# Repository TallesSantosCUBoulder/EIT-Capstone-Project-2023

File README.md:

# EIT-Capstone-Project-2023

This repository was created for the Electrical Impedance Tomography (EIT) Senior Design Project. The goals of this project were to make open-source hardware and software to reduce the cost of EIT in medical imaging.

## Demo

## Introduction
The EIT project was sponsored by Dr. Talles Santos for Colorado Mesa - Colorado Boulder Partnership engineering senior design class. 

First Year Team: Diego Sena, Keegan Erickson, Jonathan Keleppinger

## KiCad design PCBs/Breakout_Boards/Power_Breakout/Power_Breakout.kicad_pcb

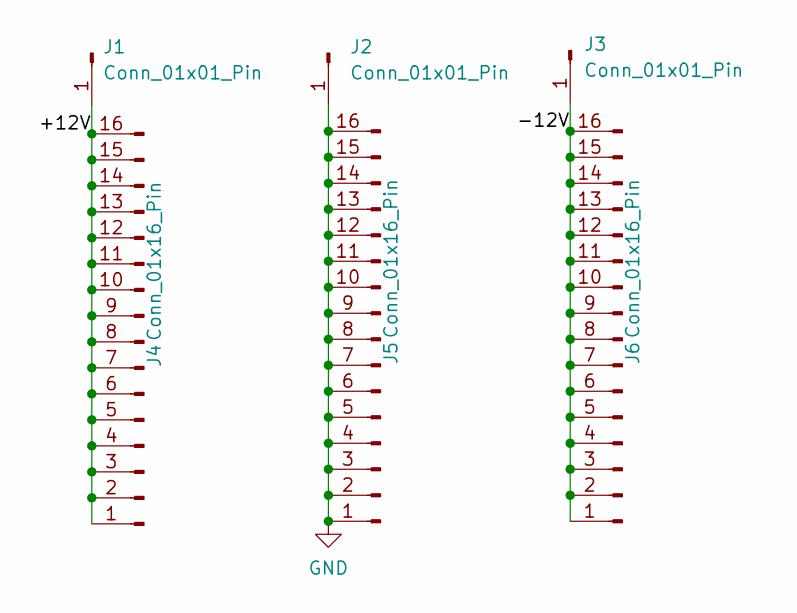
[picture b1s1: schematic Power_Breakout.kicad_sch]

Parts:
J1, J2, J3: Conn_01x01_Pin; PinHeader_1x01_P2.54mm_Vertical
J4, J5, J6: Conn_01x16_Pin; PinHeader_1x16_P2.54mm_Vertical

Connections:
/+12V: J1.1, J4.1, J4.2, J4.3, J4.4, J4.5, J4.6, J4.7, J4.8, J4.9, J4.10, J4.11, J4.12, J4.13, J4.14, J4.15, J4.16
/-12V: J3.1, J6.1, J6.2, J6.3, J6.4, J6.5, J6.6, J6.7, J6.8, J6.9, J6.10, J6.11, J6.12, J6.13, J6.14, J6.15, J6.16
GND: J2.1, J5.1, J5.2, J5.3, J5.4, J5.5, J5.6, J5.7, J5.8, J5.9, J5.10, J5.11, J5.12, J5.13, J5.14, J5.15, J5.16

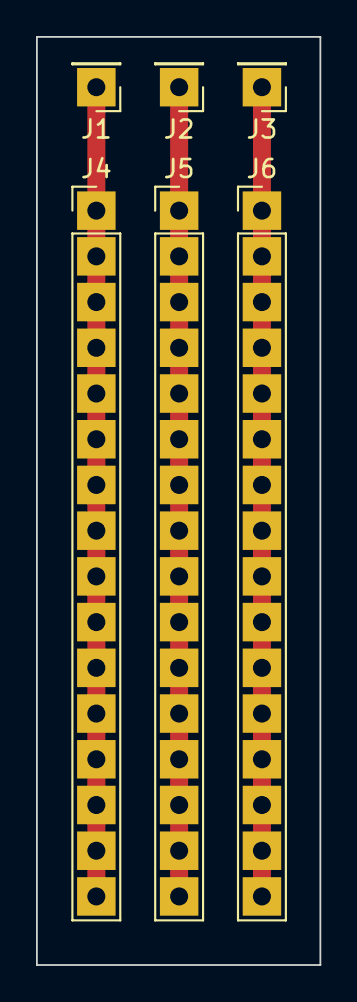
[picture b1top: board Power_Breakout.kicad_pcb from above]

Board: 2 copper layers, 15.7 x 51.6 mm, 6 parts (0 on the bottom side), 3 nets.

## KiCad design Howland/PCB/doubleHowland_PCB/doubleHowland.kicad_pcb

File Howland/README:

The Howland Current source is a Voltage Controlled Current Source

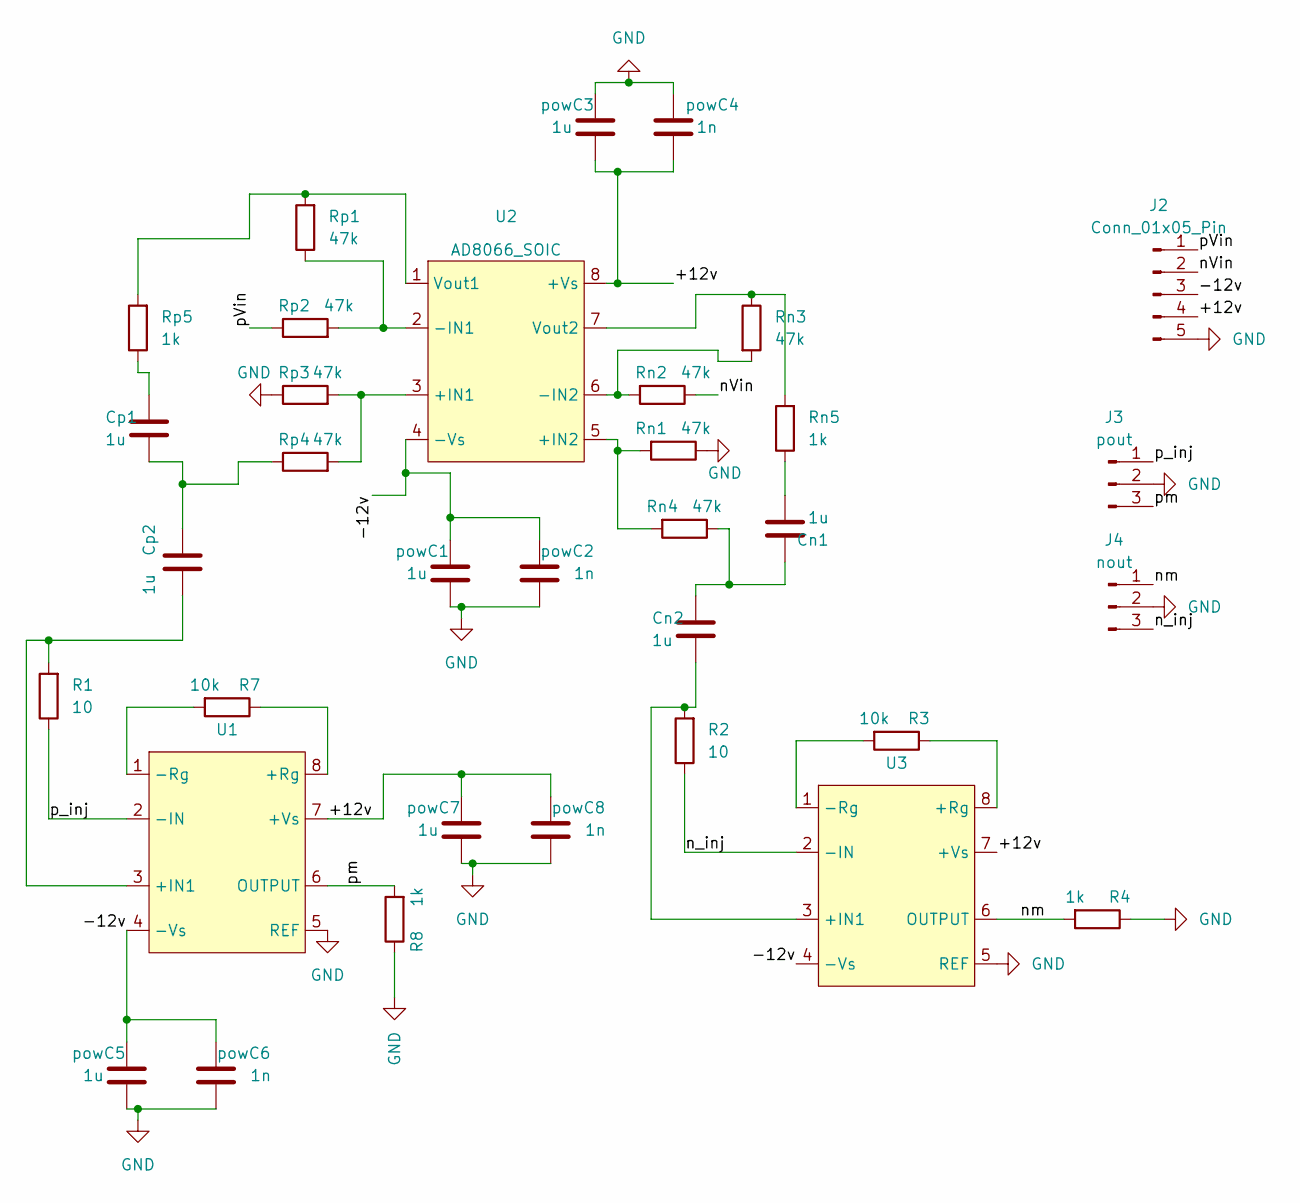
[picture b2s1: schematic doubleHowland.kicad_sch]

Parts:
Cn1, Cn2: 1u; R_Axial_DIN0207_L6.3mm_D2.5mm_P7.62mm_Horizontal
Cp1, Cp2: 1u; R_Axial_DIN0207_L6.3mm_D2.5mm_P7.62mm_Horizontal
J2: Conn_01x05_Pin; PinHeader_1x05_P2.54mm_Vertical
J3: pout; PinHeader_1x03_P2.54mm_Vertical
J4: nout; PinHeader_1x03_P2.54mm_Vertical
R1, R2: 10; R_Axial_DIN0207_L6.3mm_D2.5mm_P10.16mm_Horizontal
R3, R7: 10k; R_Axial_DIN0207_L6.3mm_D2.5mm_P10.16mm_Horizontal
R4, R8: 1k; R_Axial_DIN0207_L6.3mm_D2.5mm_P10.16mm_Horizontal
Rn1, Rn2, Rn3, Rn4: 47k; R_Axial_DIN0207_L6.3mm_D2.5mm_P10.16mm_Horizontal
Rn5: 1k; R_Axial_DIN0207_L6.3mm_D2.5mm_P10.16mm_Horizontal
Rp1, Rp2, Rp3, Rp4: 47k; R_Axial_DIN0207_L6.3mm_D2.5mm_P10.16mm_Horizontal
Rp5: 1k; R_Axial_DIN0207_L6.3mm_D2.5mm_P10.16mm_Horizontal
U1, U3: DIP-8_W7.62mm
U2: AD8066_SOIC; DIP-8_W7.62mm
powC1, powC3, powC5, powC7: 1u; R_Axial_DIN0207_L6.3mm_D2.5mm_P7.62mm_Horizontal
powC2, powC4, powC6, powC8: 1n; R_Axial_DIN0207_L6.3mm_D2.5mm_P7.62mm_Horizontal

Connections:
/+12v: J2.4, U1.7 (+Vs), U2.8 (+Vs), U3.7 (+Vs), powC3.2, powC4.2, powC7.1, powC8.1
/-12v: J2.3, U1.4 (-Vs), U2.4 (-Vs), U3.4 (-Vs), powC1.1, powC2.1, powC5.1, powC6.1
/nVin: J2.2, Rn2.1
/n_inj: J4.3, R2.1, U3.2 (-IN)
/nm: J4.1, R4.2, U3.6 (OUTPUT)
/pVin: J2.1, Rp2.1
/p_inj: J3.1, R1.1, U1.2 (-IN)
/pm: J3.3, R8.2, U1.6 (OUTPUT)
GND: J2.5, J3.2, J4.2, R4.1, R8.1, Rn1.1, Rp3.1, U1.5 (REF), U3.5 (REF), powC1.2, powC2.2, powC3.1, powC4.1, powC5.2, powC6.2, powC7.2, powC8.2
unnamed: Cn1.1, Cn2.1, Rn4.1
unnamed: Cn1.2, Rn5.1
unnamed: Cp1.1, Rp5.1
unnamed: Cp1.2, Cp2.1, Rp4.1
unnamed: Cp2.2, R1.2, U1.3 (+IN1)
unnamed: R7.1, U1.8 (+Rg)
unnamed: R7.2, U1.1 (-Rg)
unnamed: Rp3.2, Rp4.2, U2.3 (+IN1)
unnamed: Rn1.2, Rn4.2, U2.5 (+IN2)
unnamed: Rp1.1, Rp2.2, U2.2 (-IN1)
unnamed: Rn2.2, Rn3.2, U2.6 (-IN2)
unnamed: Rp1.2, Rp5.2, U2.1 (Vout1)
unnamed: Rn3.1, Rn5.2, U2.7 (Vout2)
unnamed: Cn2.2, R2.2, U3.3 (+IN1)
unnamed: R3.1, U3.8 (+Rg)
unnamed: R3.2, U3.1 (-Rg)

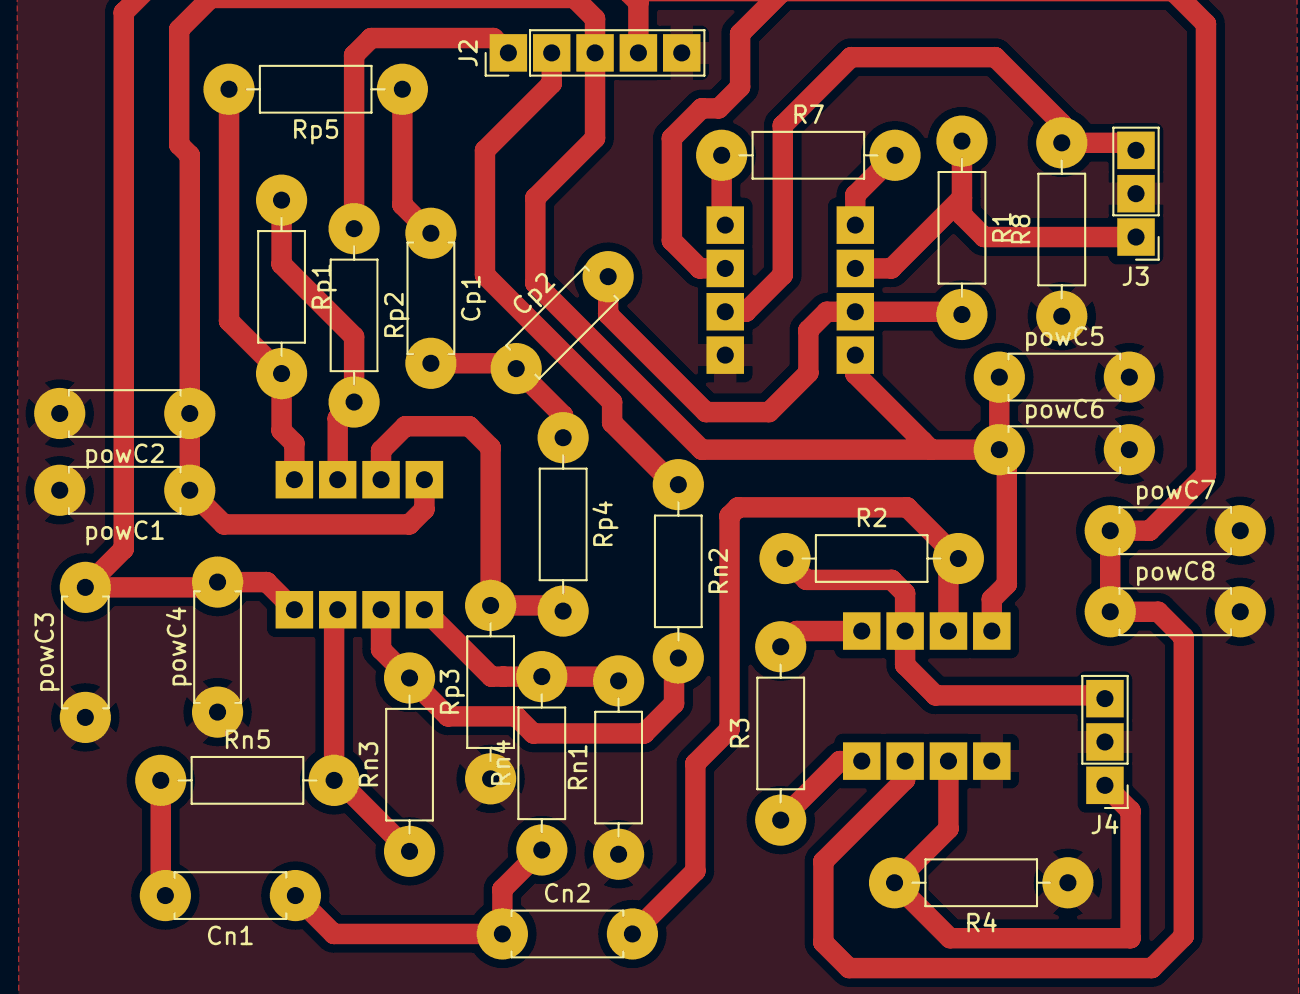
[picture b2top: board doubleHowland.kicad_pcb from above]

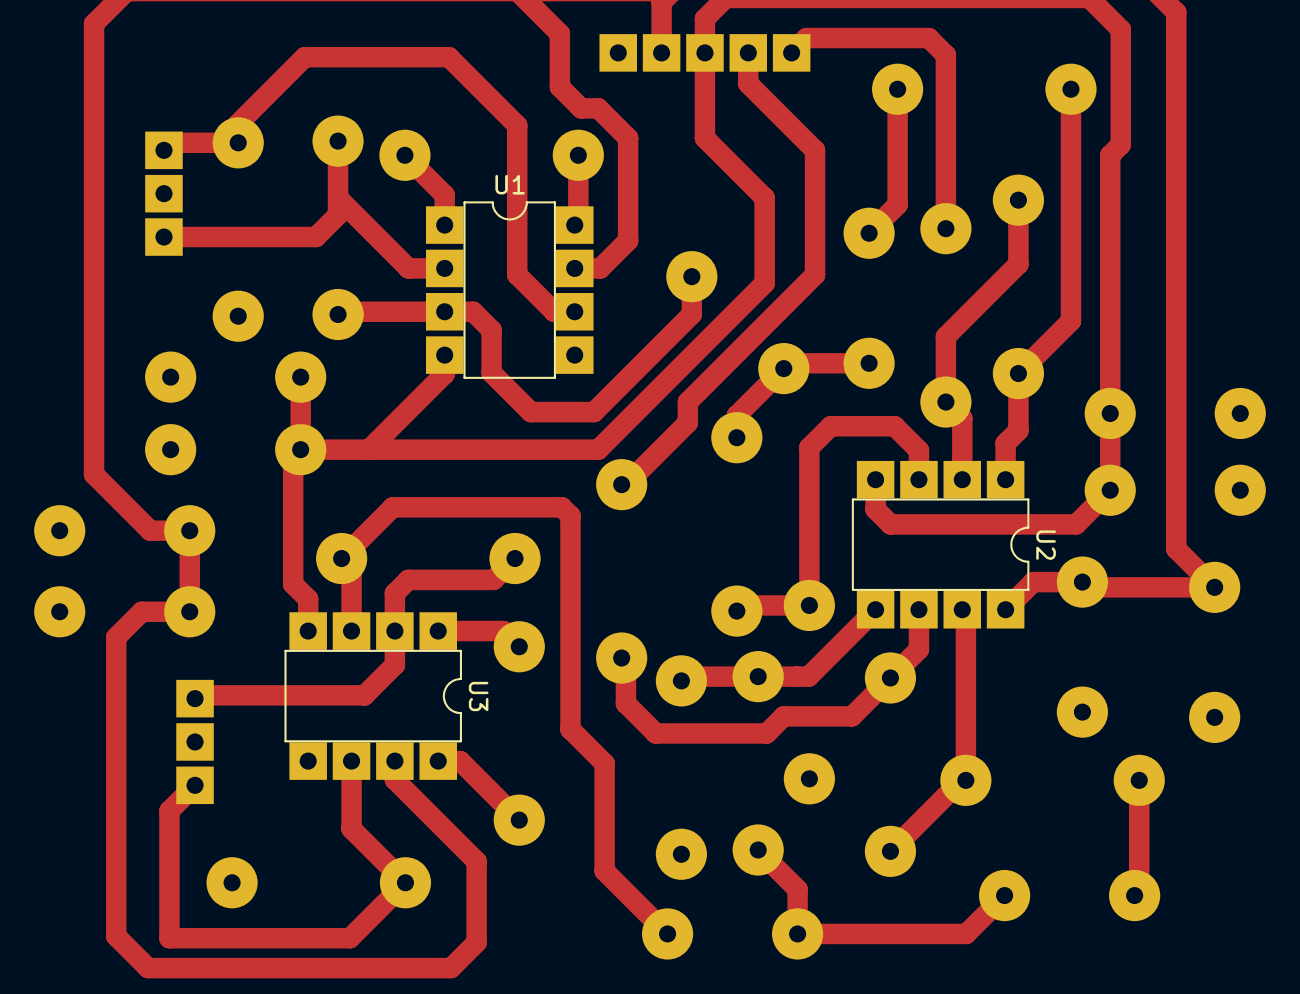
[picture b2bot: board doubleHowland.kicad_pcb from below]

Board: 2 copper layers, 34 parts (3 on the bottom side), 25 nets.

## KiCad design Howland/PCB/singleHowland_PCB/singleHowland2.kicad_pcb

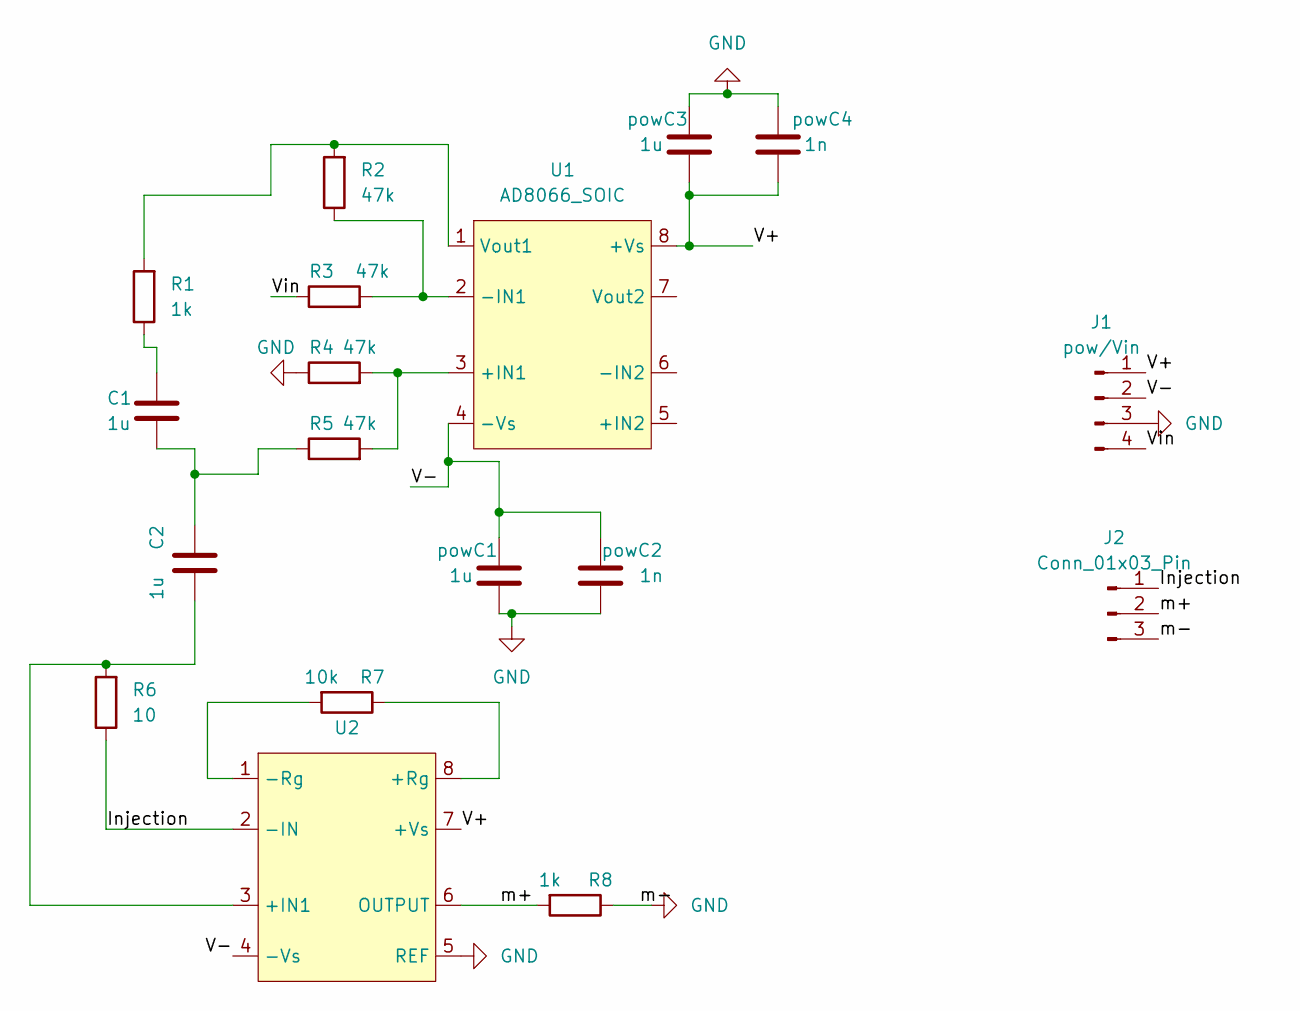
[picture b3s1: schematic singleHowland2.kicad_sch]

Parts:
C1, C2: 1u; R_Axial_DIN0207_L6.3mm_D2.5mm_P7.62mm_Horizontal
J1: pow/Vin; PinHeader_1x04_P2.54mm_Vertical
J2: Conn_01x03_Pin; PinHeader_1x03_P2.54mm_Vertical
R1, R8: 1k; R_Axial_DIN0207_L6.3mm_D2.5mm_P10.16mm_Horizontal
R2, R3, R4, R5: 47k; R_Axial_DIN0207_L6.3mm_D2.5mm_P10.16mm_Horizontal
R6: 10; R_Axial_DIN0207_L6.3mm_D2.5mm_P10.16mm_Horizontal
R7: 10k; R_Axial_DIN0207_L6.3mm_D2.5mm_P10.16mm_Horizontal
U1: AD8066_SOIC; DIP-8_W7.62mm
U2: DIP-8_W7.62mm
powC1, powC3: 1u; R_Axial_DIN0207_L6.3mm_D2.5mm_P7.62mm_Horizontal
powC2, powC4: 1n; R_Axial_DIN0207_L6.3mm_D2.5mm_P7.62mm_Horizontal

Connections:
/Injection: J2.1, R6.1, U2.2 (-IN)
/V+: J1.1, U1.8 (+Vs), U2.7 (+Vs), powC3.2, powC4.2
/V-: J1.2, U1.4 (-Vs), U2.4 (-Vs), powC1.1, powC2.1
/Vin: J1.4, R3.1
/m+: J2.2, R8.2, U2.6 (OUTPUT)
GND: J1.3, J2.3, R4.1, R8.1, U2.5 (REF), powC1.2, powC2.2, powC3.1, powC4.1
unnamed: C1.1, R1.1
unnamed: C1.2, C2.1, R5.1
unnamed: R4.2, R5.2, U1.3 (+IN1)
unnamed: R2.1, R3.2, U1.2 (-IN1)
unnamed: R1.2, R2.2, U1.1 (Vout1)
unnamed: C2.2, R6.2, U2.3 (+IN1)
unnamed: R7.1, U2.8 (+Rg)
unnamed: R7.2, U2.1 (-Rg)

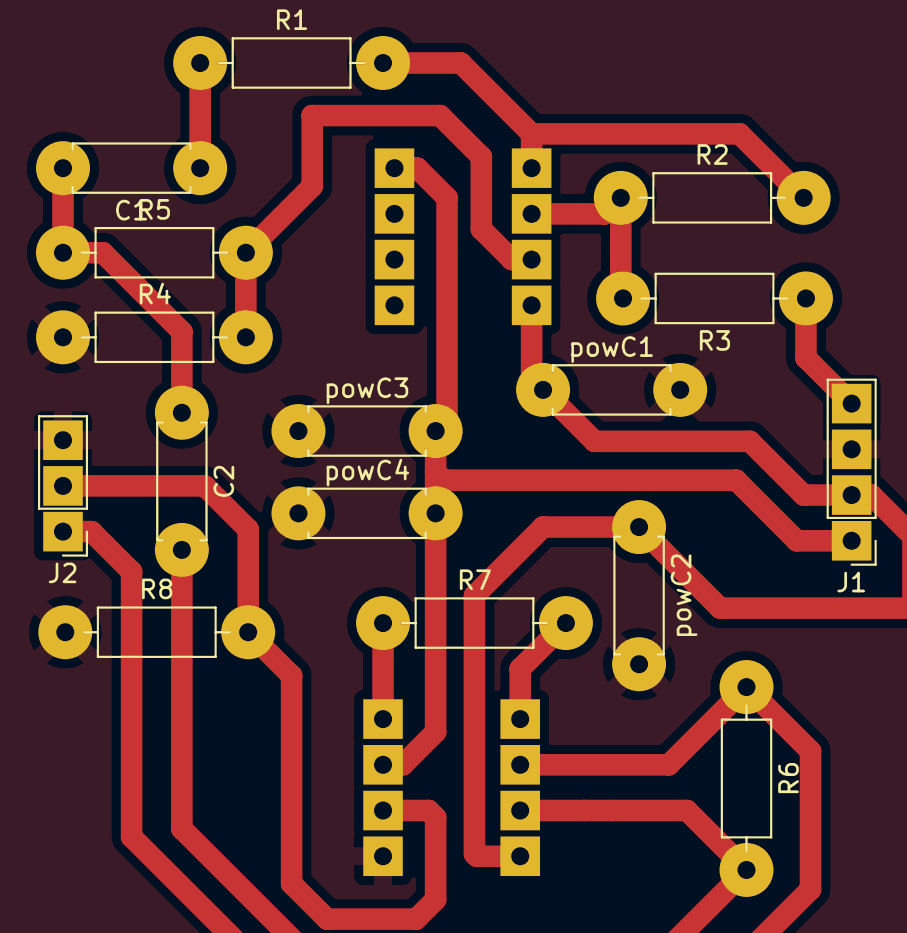
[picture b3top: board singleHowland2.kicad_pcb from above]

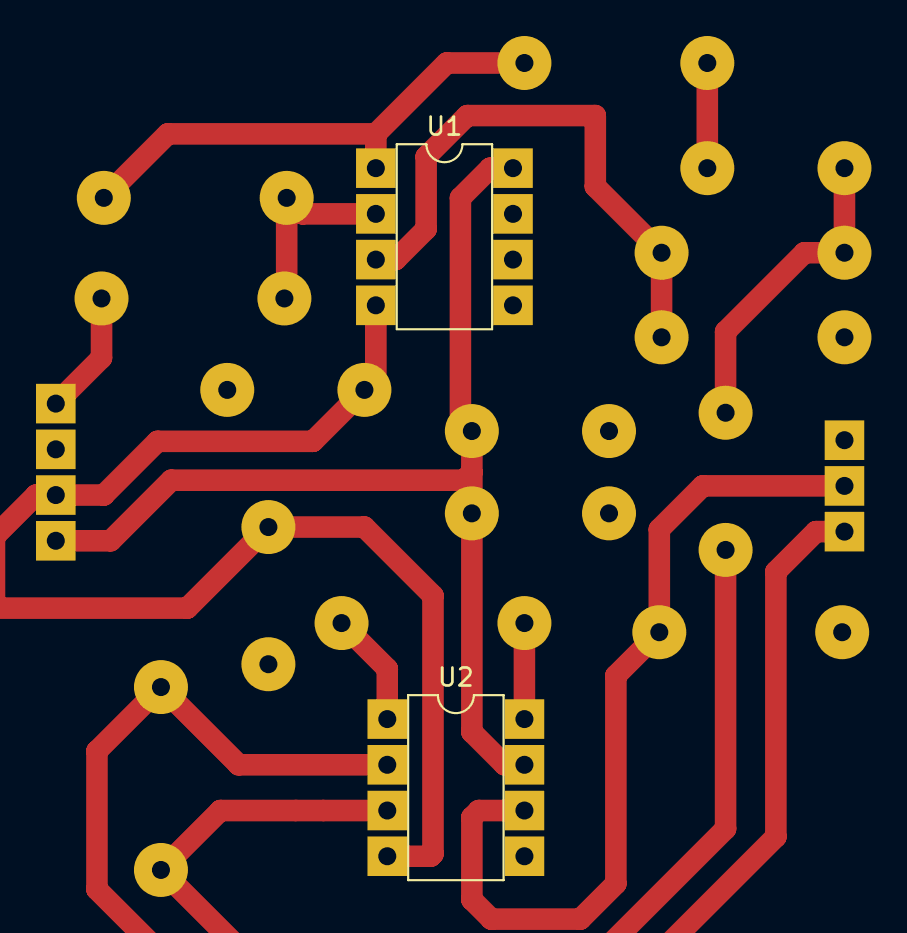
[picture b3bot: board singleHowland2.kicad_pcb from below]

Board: 2 copper layers, 18 parts (2 on the bottom side), 14 nets.

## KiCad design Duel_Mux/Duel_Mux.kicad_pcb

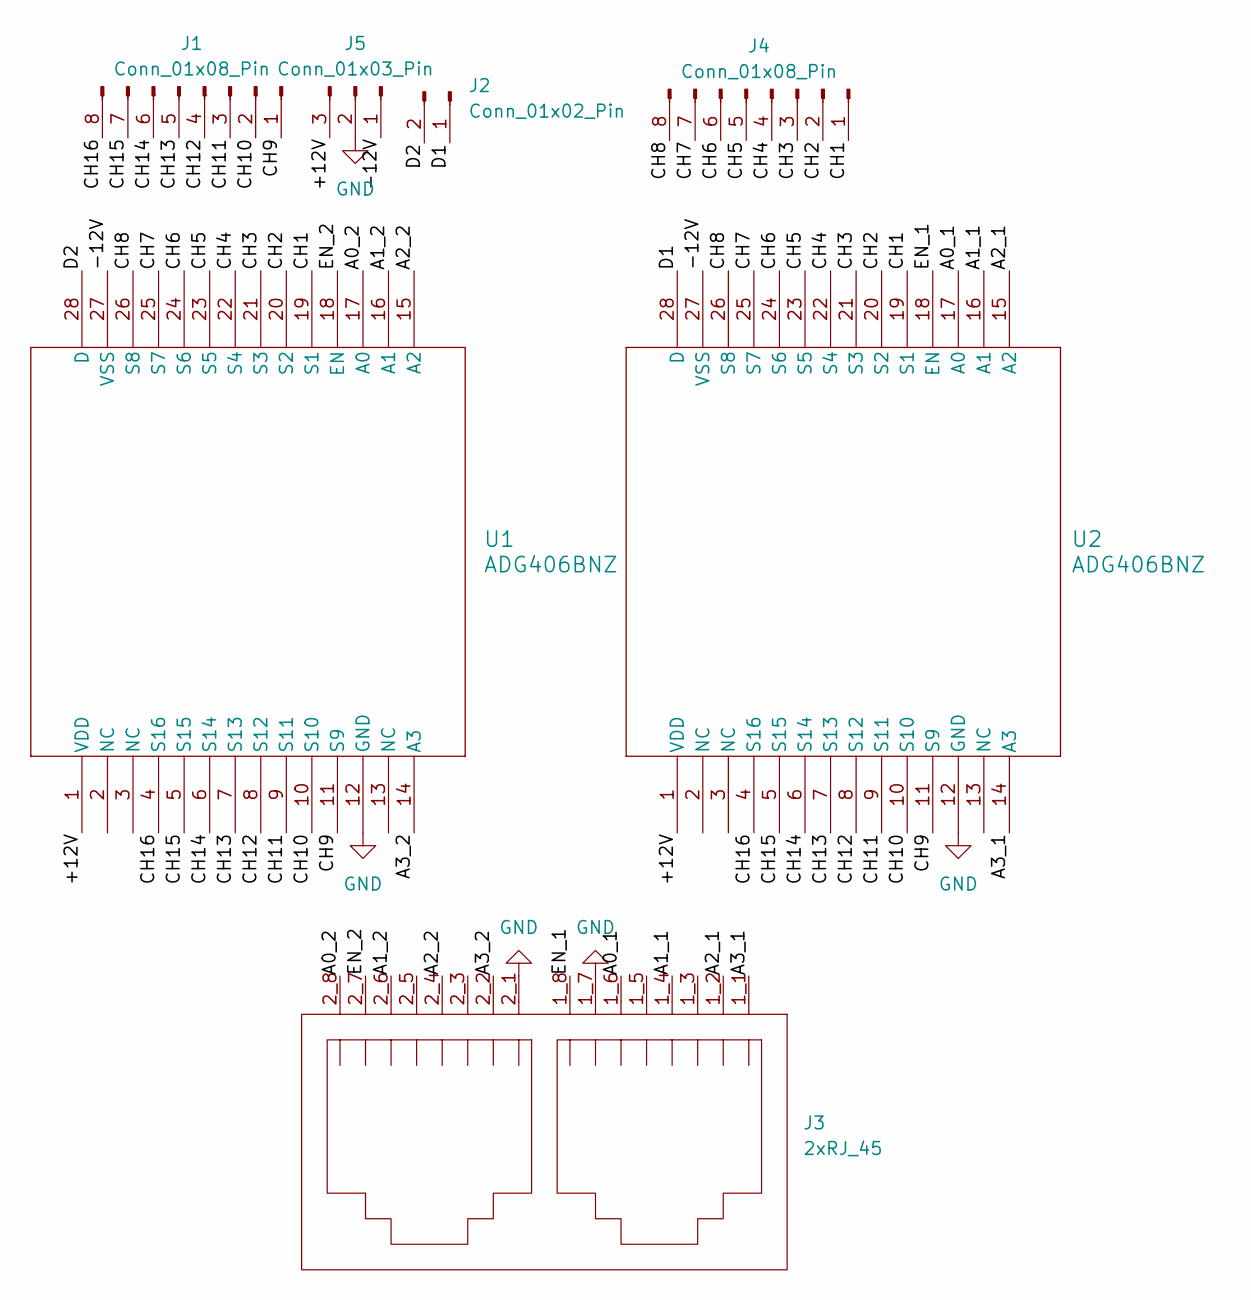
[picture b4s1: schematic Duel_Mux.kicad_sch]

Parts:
J1, J4: Conn_01x08_Pin; PinHeader_1x08_P2.54mm_Vertical
J2: Conn_01x02_Pin; PinHeader_1x02_P2.54mm_Vertical
J3: 2xRJ_45; TE_2xRJ45
J5: Conn_01x03_Pin; PinHeader_1x03_P2.54mm_Vertical
U1, U2: ADG406BNZ

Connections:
/+12V: J5.3, U1.1 (VDD), U2.1 (VDD)
/-12V: J5.1, U1.27 (VSS), U2.27 (VSS)
/A0_1: J3.1_6, U2.17 (A0)
/A0_2: J3.2_8, U1.17 (A0)
/A1_1: J3.1_4, U2.16 (A1)
/A1_2: J3.2_6, U1.16 (A1)
/A2_1: J3.1_2, U2.15 (A2)
/A2_2: J3.2_4, U1.15 (A2)
/A3_1: J3.1_1, U2.14 (A3)
/A3_2: J3.2_2, U1.14 (A3)
/CH1: J4.1, U1.19 (S1), U2.19 (S1)
/CH2: J4.2, U1.20 (S2), U2.20 (S2)
/CH3: J4.3, U1.21 (S3), U2.21 (S3)
/CH4: J4.4, U1.22 (S4), U2.22 (S4)
/CH5: J4.5, U1.23 (S5), U2.23 (S5)
/CH6: J4.6, U1.24 (S6), U2.24 (S6)
/CH7: J4.7, U1.25 (S7), U2.25 (S7)
/CH8: J4.8, U1.26 (S8), U2.26 (S8)
/CH9: J1.1, U1.11 (S9), U2.11 (S9)
/CH10: J1.2, U1.10 (S10), U2.10 (S10)
/CH11: J1.3, U1.9 (S11), U2.9 (S11)
/CH12: J1.4, U1.8 (S12), U2.8 (S12)
/CH13: J1.5, U1.7 (S13), U2.7 (S13)
/CH14: J1.6, U1.6 (S14), U2.6 (S14)
/CH15: J1.7, U1.5 (S15), U2.5 (S15)
/CH16: J1.8, U1.4 (S16), U2.4 (S16)
/D1: J2.1, U2.28 (D)
/D2: J2.2, U1.28 (D)
/EN_1: J3.1_8, U2.18 (EN)
/EN_2: J3.2_7, U1.18 (EN)
GND: J3.1_7, J3.2_1, J5.2, U1.12 (GND), U2.12 (GND)

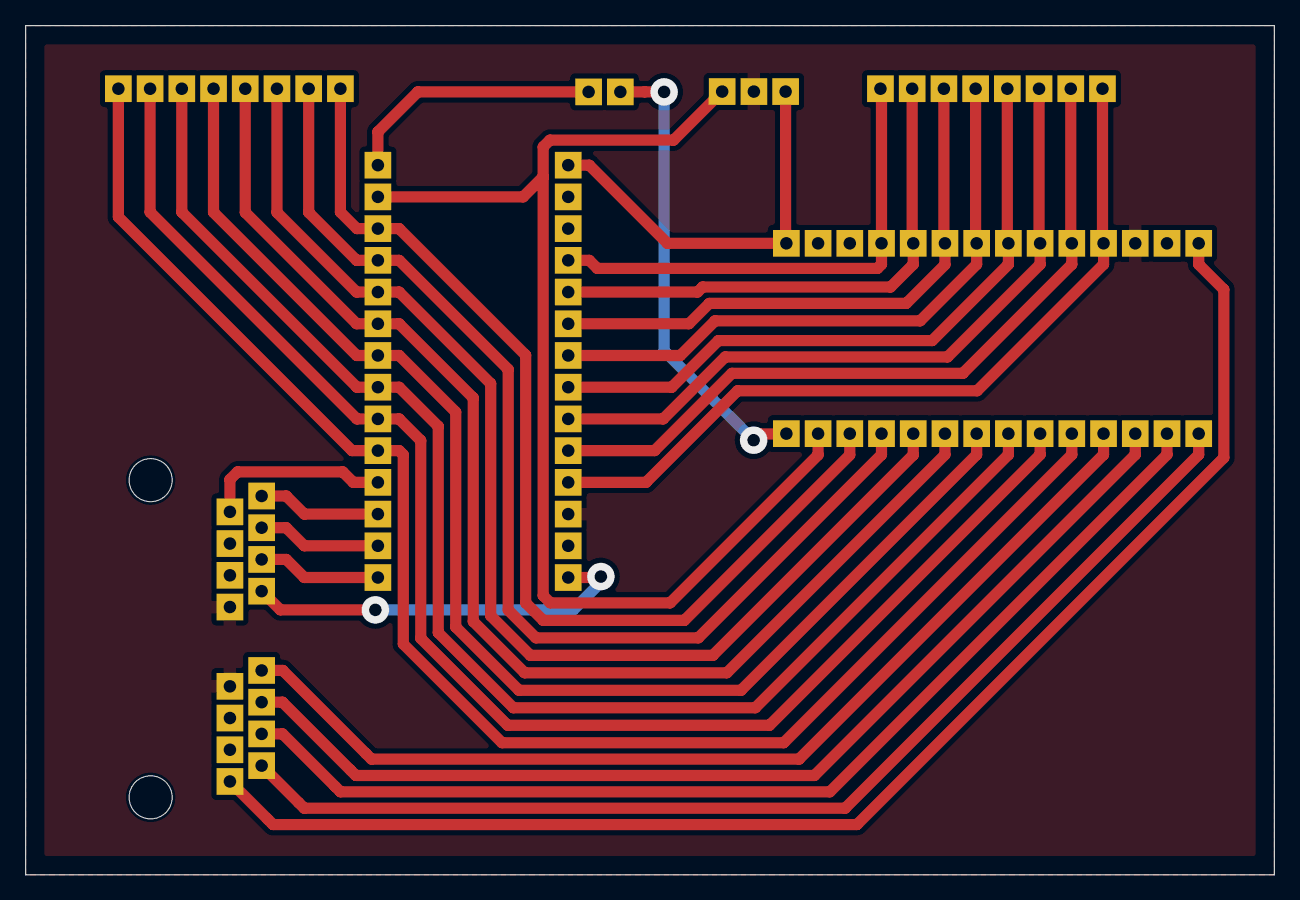
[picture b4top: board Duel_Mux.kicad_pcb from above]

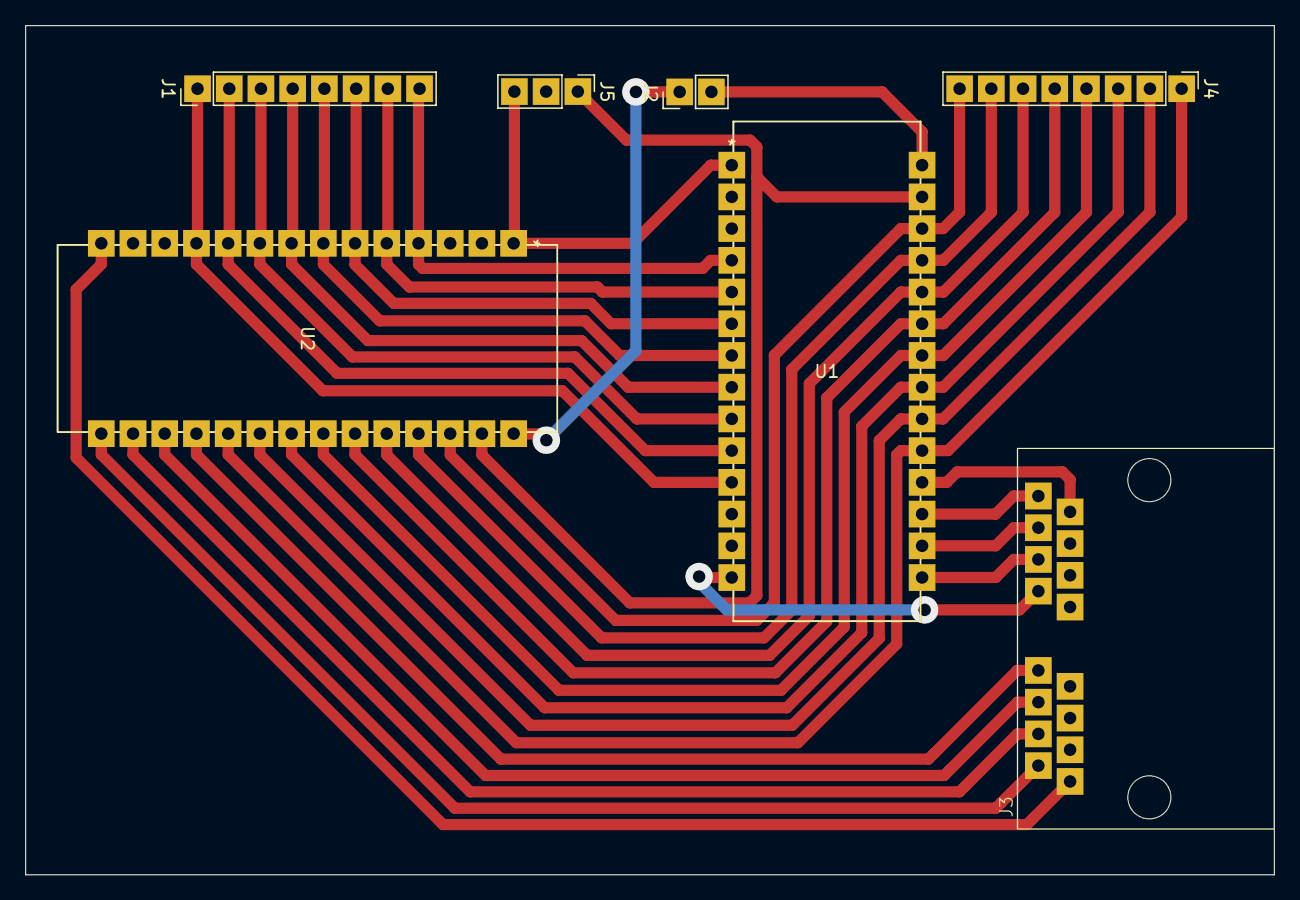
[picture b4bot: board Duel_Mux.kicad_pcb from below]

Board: 2 copper layers, 100.0 x 68.0 mm, 7 parts (7 on the bottom side), 31 nets.

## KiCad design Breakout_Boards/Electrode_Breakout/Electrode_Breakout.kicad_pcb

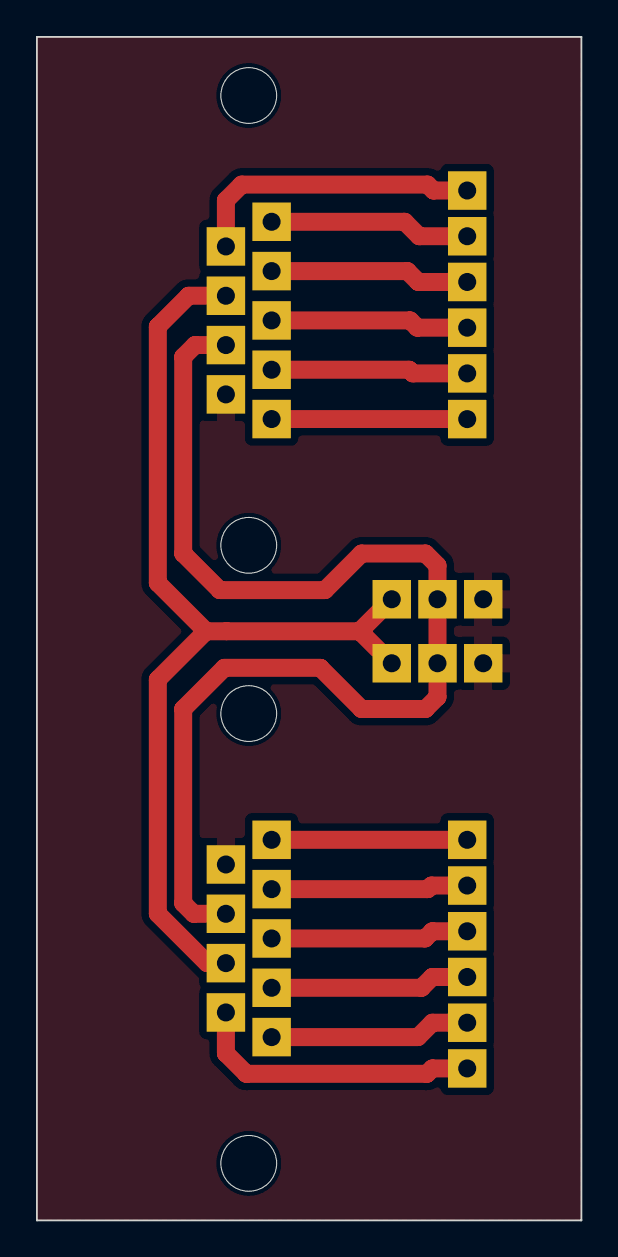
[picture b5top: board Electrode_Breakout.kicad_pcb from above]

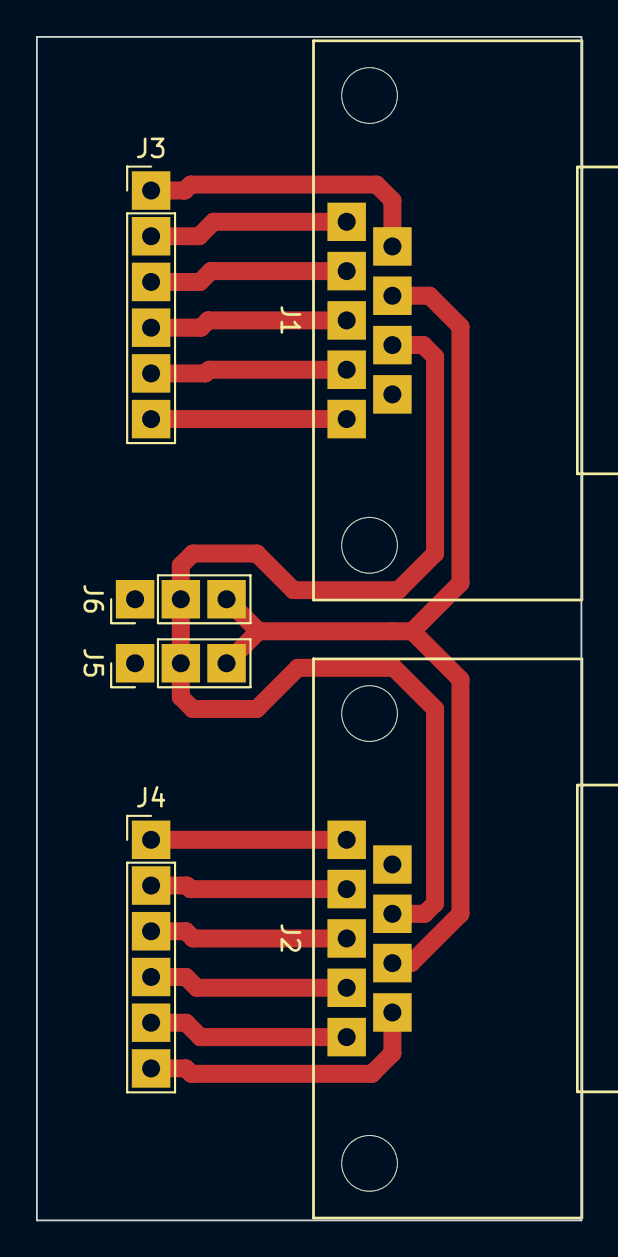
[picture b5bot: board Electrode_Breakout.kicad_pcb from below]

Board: 2 copper layers, 30.2 x 65.8 mm, 6 parts (6 on the bottom side), 15 nets.

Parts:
J1, J2: DB-9_Female
J3, J4: Conn_01x06; PinHeader_1x06_P2.54mm_Vertical
J5, J6: Conn_01x03; PinHeader_1x03_P2.54mm_Vertical

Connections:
/+12V: J1.8, J2.7, J5.3, J6.3
/-12V: J1.7, J2.8, J5.2, J6.2
/ADC1: J1.9, J3.1
/ADC2: J1.5, J3.2
/ADC3: J2.1, J4.5
/ADC4: J2.6, J4.6
/CUR1: J1.1, J3.6
/CUR2: J1.2, J3.5
/CUR3: J2.2, J4.4
/CUR4: J2.3, J4.3
/SEL1: J1.3, J3.4
/SEL2: J1.4, J3.3
/SEL3: J2.4, J4.2
/SEL4: J2.5, J4.1
GND: J1.6, J2.9, J5.1, J6.1

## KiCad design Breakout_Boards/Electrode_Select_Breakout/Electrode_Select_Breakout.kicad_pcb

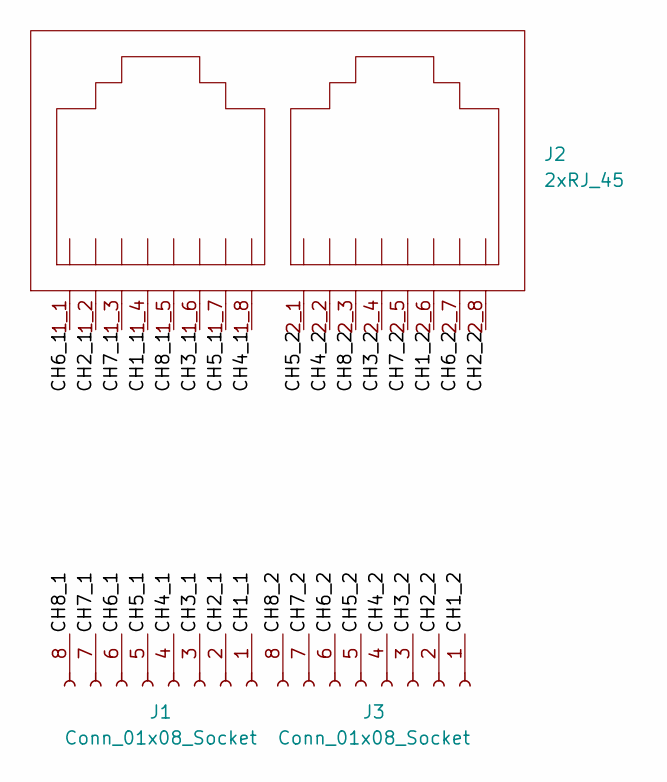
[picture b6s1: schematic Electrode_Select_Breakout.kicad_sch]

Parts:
J1, J3: Conn_01x08_Socket; PinSocket_1x08_P2.54mm_Vertical
J2: 2xRJ_45; TE_2xRJ45

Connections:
/CH1_1: J1.1, J2.1_4
/CH1_2: J2.2_6, J3.1
/CH2_1: J1.2, J2.1_2
/CH2_2: J2.2_8, J3.2
/CH3_1: J1.3, J2.1_6
/CH3_2: J2.2_4, J3.3
/CH4_1: J1.4, J2.1_8
/CH4_2: J2.2_2, J3.4
/CH5_1: J1.5, J2.1_7
/CH5_2: J2.2_1, J3.5
/CH6_1: J1.6, J2.1_1
/CH6_2: J2.2_7, J3.6
/CH7_1: J1.7, J2.1_3
/CH7_2: J2.2_5, J3.7
/CH8_1: J1.8, J2.1_5
/CH8_2: J2.2_3, J3.8

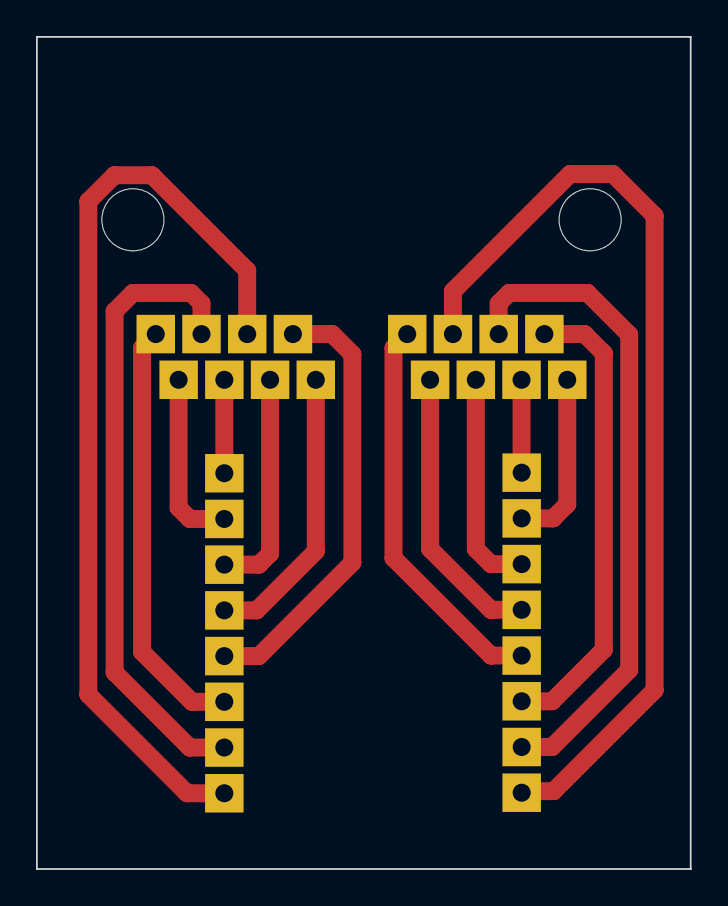
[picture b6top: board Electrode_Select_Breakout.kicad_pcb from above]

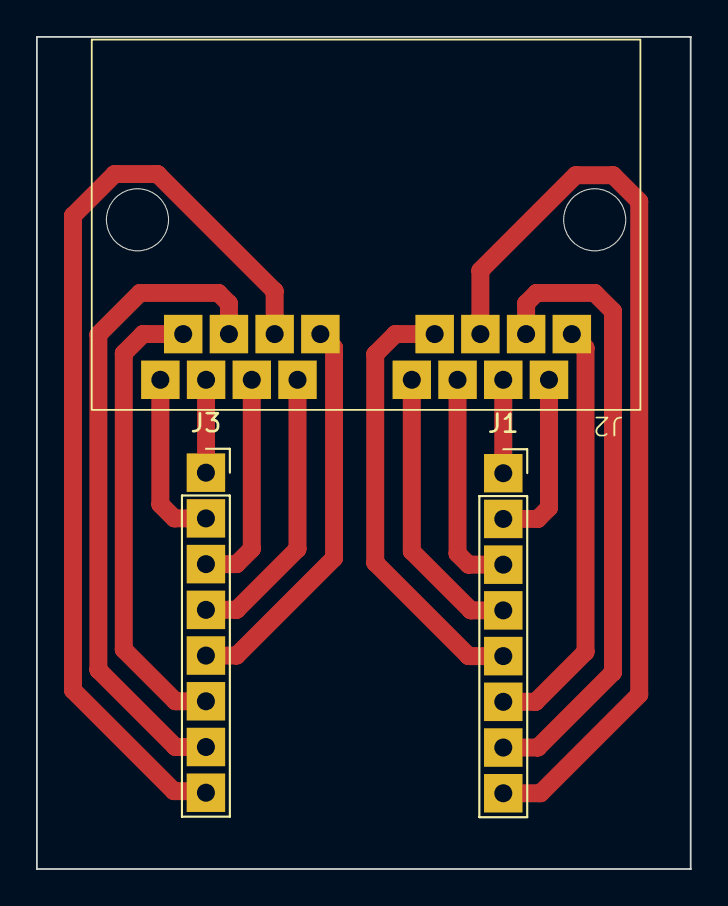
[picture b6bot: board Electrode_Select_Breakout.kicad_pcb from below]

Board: 2 copper layers, 36.3 x 46.2 mm, 3 parts (3 on the bottom side), 16 nets.

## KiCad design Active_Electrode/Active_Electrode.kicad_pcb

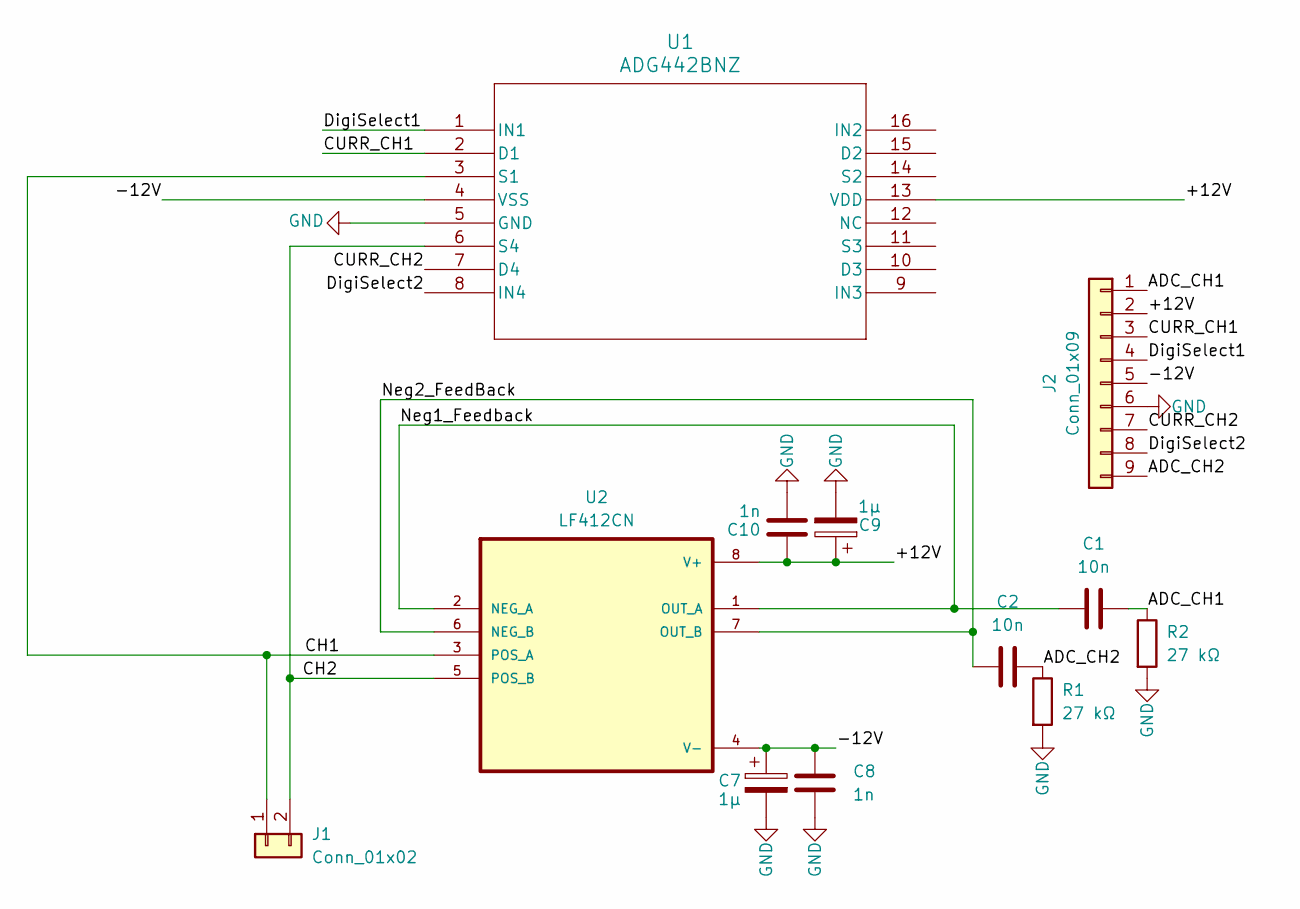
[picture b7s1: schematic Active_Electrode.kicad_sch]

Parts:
C1: 10n; C_Disc_D4.3mm_W1.9mm_P5.00mm
C2: 10n; C_Disc_D6.0mm_W2.5mm_P5.00mm
C7, C9: 1µ; CP_Radial_Tantal_D5.5mm_P5.00mm
C8: 1n; C_Disc_D6.0mm_W2.5mm_P5.00mm
C10: 1n; C_Disc_D4.3mm_W1.9mm_P5.00mm
J1: Conn_01x02; PinSocket_1x02_P2.54mm_Vertical
J2: Conn_01x09; PinSocket_1x09_P2.54mm_Vertical
R1, R2: 27 kΩ; R_Axial_DIN0207_L6.3mm_D2.5mm_P7.62mm_Horizontal
U1: ADG442BNZ; N_16_ADI
U2: LF412CN

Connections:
/+12V: C9.1, C10.1, J2.2, U1.13 (VDD), U2.8 (V+)
/-12V: C7.1, C8.1, J2.5, U1.4 (VSS), U2.4 (V-)
/ADC_CH1: C1.2, J2.1, R2.1
/ADC_CH2: C2.2, J2.9, R1.1
/CH1: J1.1, U1.3 (S1), U2.3 (POS_A)
/CH2: J1.2, U1.6 (S4), U2.5 (POS_B)
/CURR_CH1: J2.3, U1.2 (D1)
/CURR_CH2: J2.7, U1.7 (D4)
/DigiSelect1: J2.4, U1.1 (IN1)
/DigiSelect2: J2.8, U1.8 (IN4)
/Neg1_Feedback: C1.1, U2.1 (OUT_A), U2.2 (NEG_A)
/Neg2_FeedBack: C2.1, U2.6 (NEG_B), U2.7 (OUT_B)
GND: C7.2, C8.2, C9.2, C10.2, J2.6, R1.2, R2.2, U1.5 (GND)

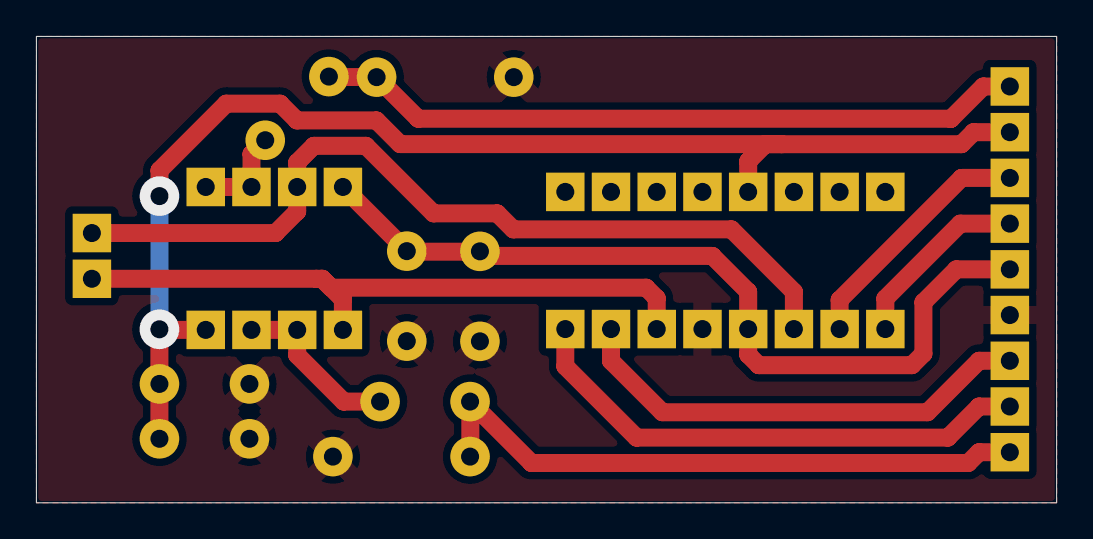
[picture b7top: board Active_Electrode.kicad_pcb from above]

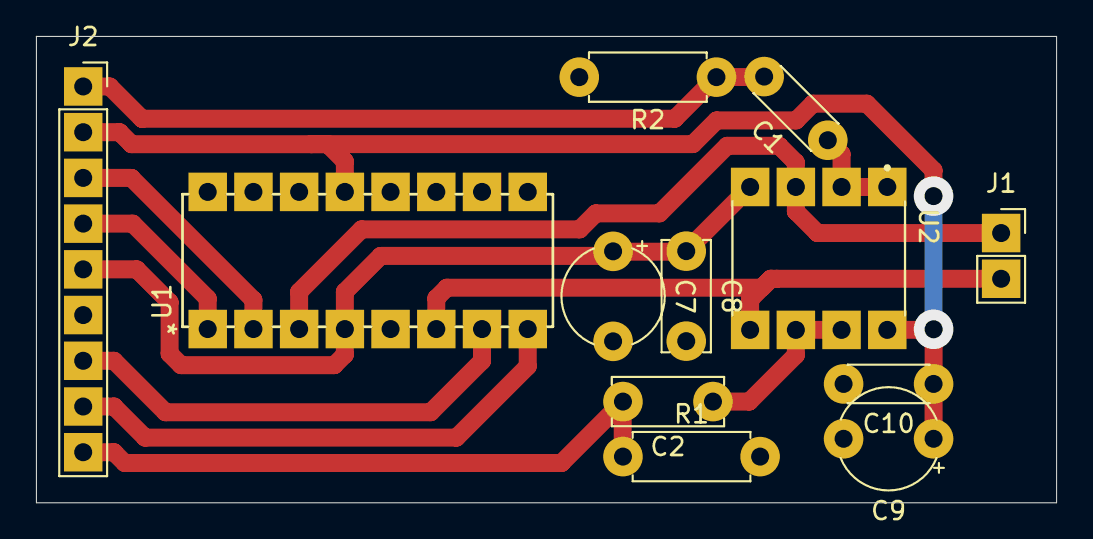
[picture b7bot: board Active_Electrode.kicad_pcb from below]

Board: 2 copper layers, 56.7 x 25.9 mm, 12 parts (12 on the bottom side), 13 nets.
